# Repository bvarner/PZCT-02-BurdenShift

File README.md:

# PZCT-02-BurdenShift
Resistive burden &amp; level shift to convert PZCT-02 Split-core Current Transformer output to ADC input voltages.

In searching for split-core current transformers, I ran across the PZCT-02. A rather inexpensive split-core 100 Amp transformer.
[Amazon](https://www.amazon.com/s?k=PZCT-02+current+transformer)
[AliExpress](https://www.aliexpress.com/wholesale?SearchText=PZCT-02)

This circuit provides burden resistance, voltage division & test point shifting to feed measurements into an Analog to Digital Converter (ADC).

I've used this with the 10bit analog input pins on Arduino's, as well as an ADS1115 16-bit ADC hooked to a raspberry pi I2C bus.

Both approaches work well. But I prefer the 16bit resolution on the I2C bus of the Pi, which can be polled rediculously fast using Collectd and the 'sensors' plugin.

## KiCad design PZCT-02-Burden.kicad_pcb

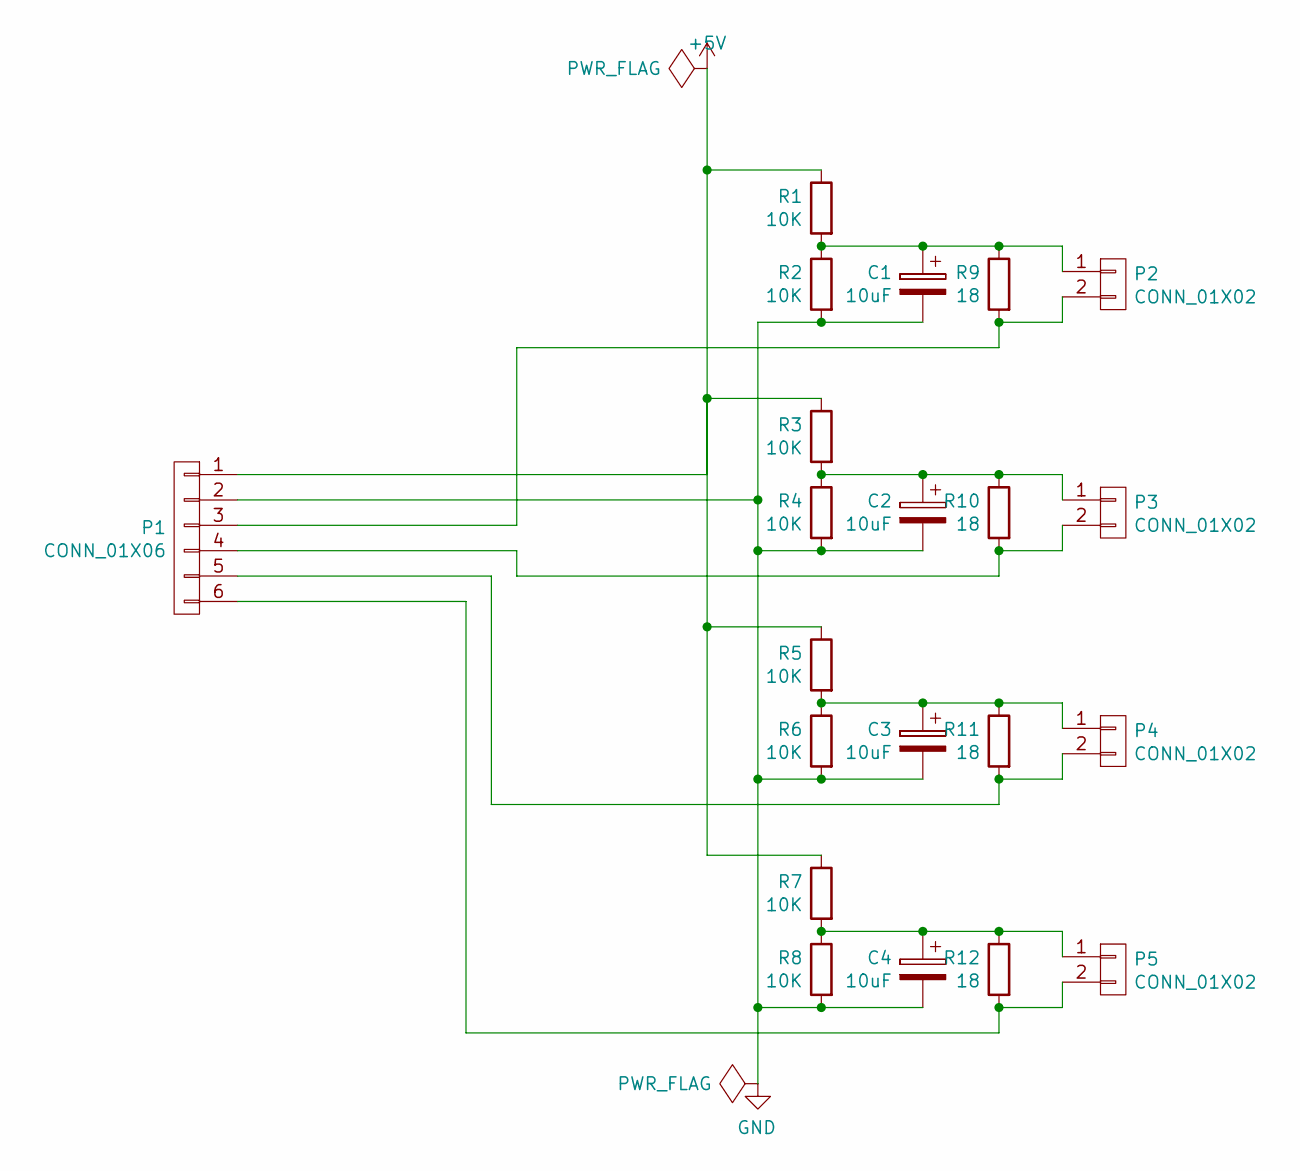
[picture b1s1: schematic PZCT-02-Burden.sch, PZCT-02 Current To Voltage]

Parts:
C1, C2, C3, C4: 10uF; C_Radial_D5_L11_P2
P1: CONN_01X06; Pin_Header_Straight_1x06
P2, P3, P4, P5: CONN_01X02; Pin_Header_Straight_1x02
R1, R2, R3, R4, R5, R6, R7, R8: 10K; Resistor_Horizontal_RM7mm
R9, R10, R11, R12: 18; Resistor_Horizontal_RM15mm

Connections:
+5V: P1.1, R1.1, R3.1, R5.1, R7.1
GND: C1.2, C2.2, C3.2, C4.2, P1.2, R2.2, R4.2, R6.2, R8.2
unnamed: C1.1, P2.1, R1.2, R2.1, R9.1
unnamed: C2.1, P3.1, R3.2, R4.1, R10.1
unnamed: C3.1, P4.1, R5.2, R6.1, R11.1
unnamed: C4.1, P5.1, R7.2, R8.1, R12.1
unnamed: P1.3, P2.2, R9.2
unnamed: P1.4, P3.2, R10.2
unnamed: P1.5, P4.2, R11.2
unnamed: P1.6, P5.2, R12.2

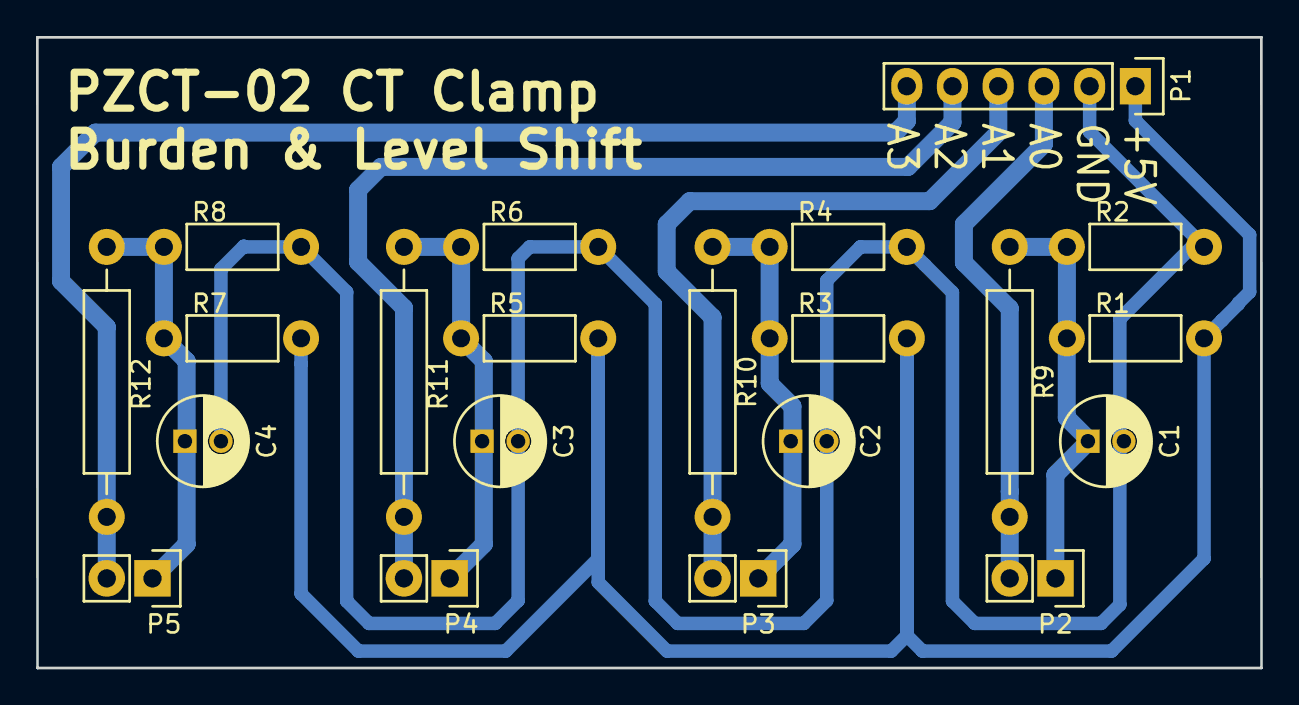
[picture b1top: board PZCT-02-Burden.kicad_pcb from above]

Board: 2 copper layers, 68.0 x 35.0 mm, 21 parts (0 on the bottom side), 10 nets.

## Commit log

2017-04-05 Initial commit and what-not
2017-04-05 plots
2019-12-03 Update README.md
    Updated to include non-specific links for search terms from multiple sellers.
